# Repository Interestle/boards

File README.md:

# boards
Here lies a bunch of random board designs I have made to various reasons. Most are simple designs purely made to solve a simple issue.

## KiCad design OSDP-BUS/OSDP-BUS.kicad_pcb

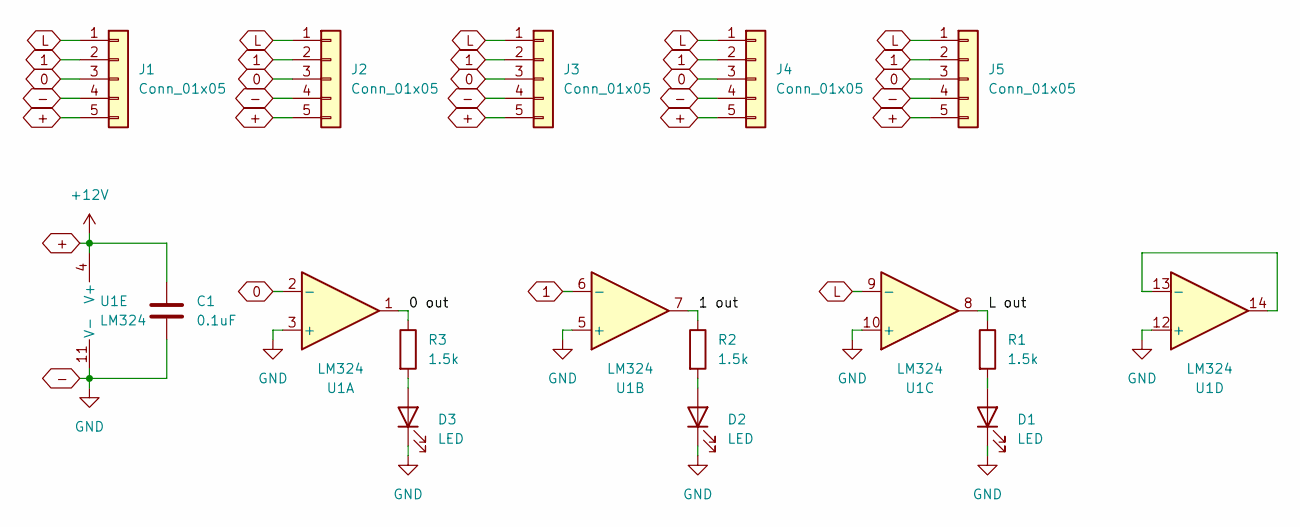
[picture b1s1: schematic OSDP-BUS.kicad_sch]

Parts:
C1: 0.1uF; C_0402_1005Metric_Pad0.74x0.62mm_HandSolder
D1, D2, D3: LED; LED_0603_1608Metric_Pad1.05x0.95mm_HandSolder
J1, J2, J3, J4, J5: Conn_01x05; PhoenixContact_MCV_1,5_5-G-3.5_1x05_P3.50mm_Vertical
R1, R2, R3: 1.5k; R_0603_1608Metric_Pad0.98x0.95mm_HandSolder
U1: LM324; SOIC-14_3.9x8.7mm_P1.27mm

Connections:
0: J1.3, J2.3, J3.3, J4.3, J5.3, U1.2 (-)
1: J1.2, J2.2, J3.2, J4.2, J5.2, U1.6 (-)
+: C1.1, J1.5, J2.5, J3.5, J4.5, J5.5, U1.4 (V+)
-: C1.2, D1.1 (K), D2.1 (K), D3.1 (K), J1.4, J2.4, J3.4, J4.4, J5.4, U1.3 (+), U1.5 (+), U1.10 (+), U1.11 (V-), U1.12 (+)
/0 out: R3.1, U1.1
/1 out: R2.1, U1.7
/L out: R1.1, U1.8
L: J1.1, J2.1, J3.1, J4.1, J5.1, U1.9 (-)
unnamed: D1.2 (A), R1.2
unnamed: D2.2 (A), R2.2
unnamed: D3.2 (A), R3.2
unnamed: U1.13 (-), U1.14

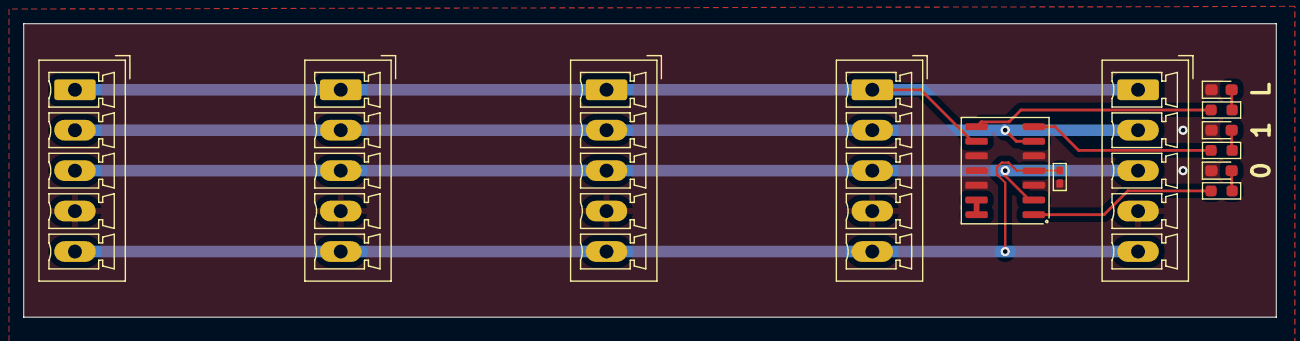
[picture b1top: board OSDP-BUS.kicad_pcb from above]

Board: 2 copper layers, 108.4 x 25.4 mm, 13 parts (0 on the bottom side), 12 nets.

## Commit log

2023-08-04 Add OSDP bus. A simple solution to multi-drop multiple OSDP readers to a single access control unit
